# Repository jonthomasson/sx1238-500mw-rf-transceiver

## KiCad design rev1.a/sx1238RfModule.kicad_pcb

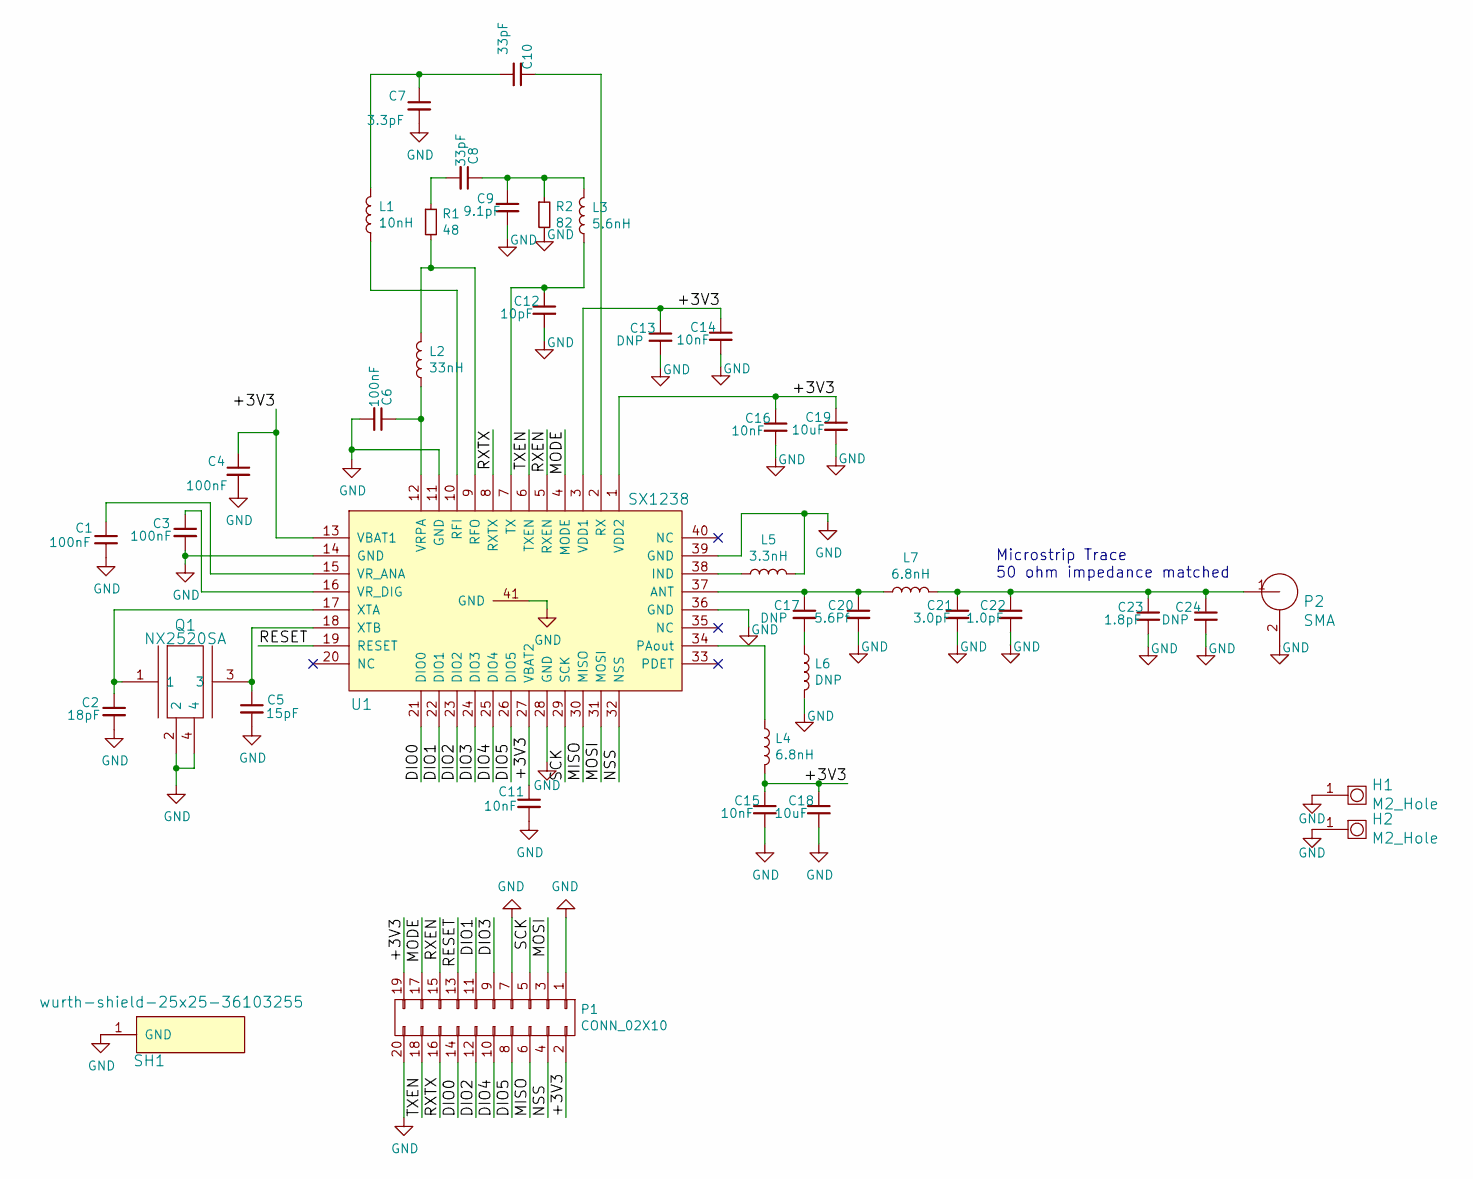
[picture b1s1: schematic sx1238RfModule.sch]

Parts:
C1, C3, C4, C6: 100nF; murata-cap-0402
C2: 18pF; murata-cap-0402
C5: 15pF; murata-cap-0402
C7: 3.3pF; murata-cap-0402
C8, C10: 33pF; murata-cap-0402
C9: 9.1pF; murata-cap-0402
C11, C14, C15, C16: 10nF; murata-cap-0402
C12: 10pF; murata-cap-0402
C13, C17, C24: DNP; murata-cap-0402
C18, C19: 10uF; murata-cap-0603
C20: 5.6Pf; murata-cap-0402
C21: 3.0pF; murata-cap-0402
C22: 1.0pF; murata-cap-0402
C23: 1.8pF; murata-cap-0402
H1, H2: M2_Hole; M2_2.2mm_mounting_hole
L1: 10nH; murata-inductor-0402
L2: 33nH; murata-inductor-0402
L3: 5.6nH; murata-inductor-0402
L4, L7: 6.8nH; murata-inductor-0402
L5: 3.3nH; murata-inductor-0402
L6: DNP; murata-inductor-0402
P1: CONN_02X10; Pin_Header_Straight_2x10
P2: SMA; 0732511150
Q1: NX2520SA; ndk-NX2520SA-32.000000MHZ
R1: 48; R_0402
R2: 82; R_0402
SH1: wurth-shield-25x25-36103255
U1: SX1238; semtech-sx1238

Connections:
/+3V3: C4.1, C11.1, C13.1, C14.1, C15.1, C16.1, C18.1, C19.1, L4.2, P1.2, P1.19, U1.1 (VDD2), U1.3 (VDD1), U1.13 (VBAT1), U1.27 (VBAT2)
/DIO0: P1.14, U1.21 (DIO0)
/DIO1: P1.11, U1.22 (DIO1)
/DIO2: P1.12, U1.23 (DIO2)
/DIO3: P1.9, U1.24 (DIO3)
/DIO4: P1.10, U1.25 (DIO4)
/DIO5: P1.8, U1.26 (DIO5)
/MISO: P1.6, U1.30 (MISO)
/MODE: P1.17, U1.4 (MODE)
/MOSI: P1.3, U1.31 (MOSI)
/NSS: P1.4, U1.32 (NSS)
/RESET: P1.13, U1.19 (RESET)
/RXEN: P1.15, U1.5 (RXEN)
/RXTX: P1.16, U1.8 (RXTX)
/SCK: P1.5, U1.29 (SCK)
/TXEN: P1.18, U1.6 (TXEN)
GND: C1.2, C2.2, C3.2, C4.2, C5.2, C6.2, C7.2, C9.2, C11.2, C12.2, C13.2, C14.2, C15.2, C16.2, C18.2, C19.2, C20.2, C21.2, C22.2, C23.2, C24.2, H1.1, H2.1, L5.2, L6.2, P1.1, P1.7, P1.20, P2.2, Q1.2, Q1.4, R2.2, SH1.1, U1.11 (GND), U1.14 (GND), U1.28 (GND), U1.36 (GND), U1.39 (GND), U1.41 (GND)
unnamed: C1.1, U1.15 (VR_ANA)
unnamed: C2.1, Q1.1, U1.17 (XTA)
unnamed: C3.1, U1.16 (VR_DIG)
unnamed: C5.1, Q1.3, U1.18 (XTB)
unnamed: C6.1, L2.1, U1.12 (VRPA)
unnamed: C8.1, C9.1, L3.2, R2.1
unnamed: C8.2, R1.1
unnamed: C10.1, U1.2 (RX)
unnamed: C7.1, C10.2, L1.2
unnamed: C12.1, L3.1, U1.7 (TX)
unnamed: C17.1, C20.1, L7.1, U1.37 (ANT)
unnamed: C17.2, L6.1
unnamed: C21.1, C22.1, C23.1, C24.1, L7.2, P2.1
unnamed: L1.1, U1.10 (RFI)
unnamed: L2.2, R1.2, U1.9 (RFO)
unnamed: L4.1, U1.34 (PAout)
unnamed: L5.1, U1.38 (IND)

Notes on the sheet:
Microstrip Trace 50 ohm impedance matched

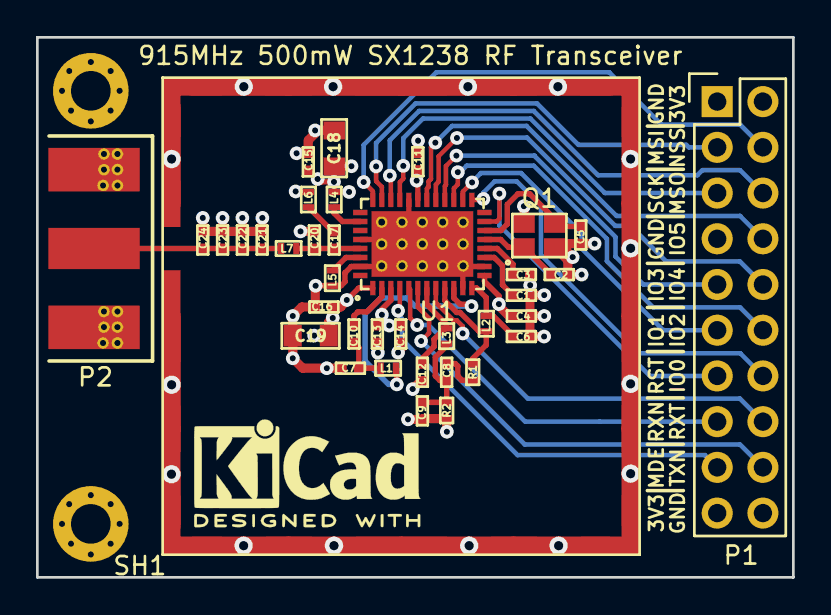
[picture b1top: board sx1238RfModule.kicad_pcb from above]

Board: 4 copper layers, 42.0 x 30.0 mm, 40 parts (0 on the bottom side), 34 nets.

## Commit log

2018-02-06 :tada: Added .gitattributes & .gitignore files
2018-03-26 added BOM
